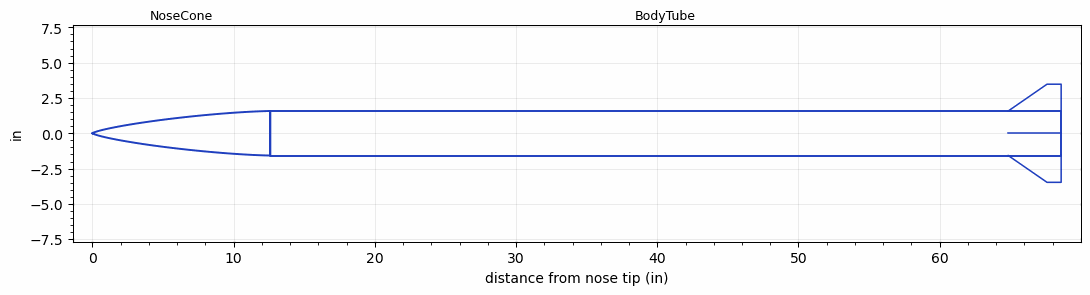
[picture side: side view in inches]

<RASAeroDocument>
 <FileVersion>2</FileVersion>
 <RocketDesign>
  <NoseCone>
   <Length>12.6</Length>
   <Diameter>3.15</Diameter>
   <Shape>Von Karman Ogive</Shape>
   <Location>0</Location>
  </NoseCone>
  <BodyTube>
   <Length>56</Length>
   <Diameter>3.15</Diameter>
   <RailGuideDiameter>0.2</RailGuideDiameter>
   <RailGuideHeight>0.2</RailGuideHeight>
   <Location>12.6</Location>
   <Fin>
    <Count>4</Count>
    <Chord>3.75</Chord>
    <Span>1.9</Span>
    <SweepDistance>2.75</SweepDistance>
    <TipChord>1</TipChord>
    <Thickness>0.12</Thickness>
    <LERadius>0.1</LERadius>
    <Location>3.75</Location>
    <AirfoilSection>Hexagonal</AirfoilSection>
    <FX1>0.2</FX1>
    <FX3>0.2</FX3>
   </Fin>
  </BodyTube>
  <Surface>Smooth (Zero Roughness)</Surface>
  <ModifiedBarrowman>False</ModifiedBarrowman>
  <Turbulence>False</Turbulence>
  <UseBooster1>False</UseBooster1>
  <UseBooster2>False</UseBooster2>
 </RocketDesign>
 <LaunchSite>
  <Altitude>0</Altitude>
  <Pressure>0</Pressure>
  <RodAngle>0</RodAngle>
  <RodLength>4</RodLength>
  <Temperature>74</Temperature>
  <WindSpeed>0</WindSpeed>
 </LaunchSite>
 <Recovery>
  <Altitude1>1000</Altitude1>
  <Altitude2>1000</Altitude2>
  <DeviceType1>None</DeviceType1>
  <DeviceType2>None</DeviceType2>
  <Event1>False</Event1>
  <Event2>False</Event2>
  <Size1>1</Size1>
  <Size2>1</Size2>
  <EventType1>None</EventType1>
  <EventType2>None</EventType2>
  <CD1>1.33</CD1>
  <CD2>1.33</CD2>
 </Recovery>
 <SimulationList>
  <Simulation>
   <SustainerEngine>K1440  (CTI)</SustainerEngine>
   <SustainerLaunchWt>17</SustainerLaunchWt>
   <SustainerNozzleDiameter>2.1</SustainerNozzleDiameter>
   <SustainerCG>39.4</SustainerCG>
   <SustainerIgnitionDelay>0</SustainerIgnitionDelay>
   <Booster1SeparationDelay>0</Booster1SeparationDelay>
   <Booster1IgnitionDelay>0</Booster1IgnitionDelay>
   <IncludeBooster1>False</IncludeBooster1>
   <Booster2Delay>0</Booster2Delay>
   <IncludeBooster2>False</IncludeBooster2>
   <TimetoApogee>24.89047</TimetoApogee>
   <MaxAltitude>10915.28</MaxAltitude>
   <MaxVelocity>1012.088</MaxVelocity>
   <OptimumWt>10.125</OptimumWt>
   <OptimumMaxAlt>10.125</OptimumMaxAlt>
  </Simulation>
 </SimulationList>
</RASAeroDocument>
